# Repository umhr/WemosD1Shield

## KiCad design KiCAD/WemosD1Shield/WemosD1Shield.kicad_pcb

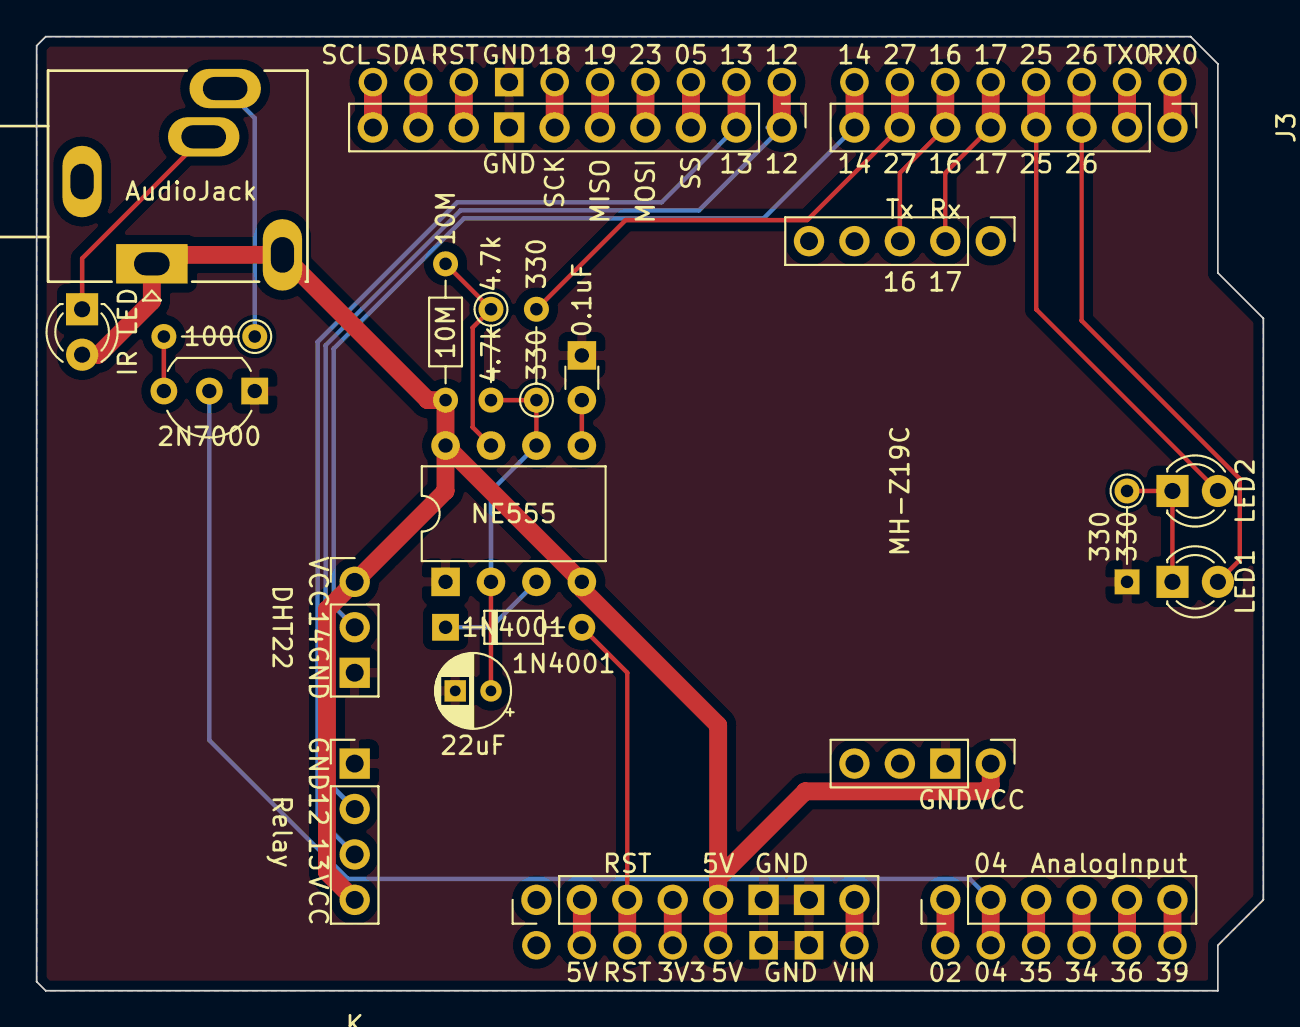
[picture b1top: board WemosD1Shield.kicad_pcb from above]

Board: 2 copper layers, 68.6 x 53.3 mm, 23 parts (1 on the bottom side), 37 nets.

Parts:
0.1uF: 0.1uF; C_Disc_D3.0mm_W1.6mm_P2.50mm
1N4001: 1N4001; D_DO-34_SOD68_P7.62mm_Horizontal
2N7000: Q_NPN_EBC; TO-92_Inline_Wide
04: Conn_01x06; PinHeader_1x06_P2.54mm_Vertical
4.7k: 4.7k; R_Axial_DIN0204_L3.6mm_D1.6mm_P5.08mm_Vertical
10M: 10M; R_Axial_DIN0204_L3.6mm_D1.6mm_P7.62mm_Horizontal
22uF: 22uF; CP_Radial_D4.0mm_P2.00mm
100: R; R_Axial_DIN0204_L3.6mm_D1.6mm_P5.08mm_Vertical
330, 330#2: 330; R_Axial_DIN0204_L3.6mm_D1.6mm_P5.08mm_Vertical
A1: Arduino_UNO_R3
AudioJack: AudioJack3_SwitchTR; Jack_3.5mm_Ledino_KB3SPRS_Horizontal
DHT22: DHT22; PinHeader_1x03_P2.54mm_Vertical
IR LED: LED; LED_D3.0mm_Clear
J3: Conn_01x08; PinHeader_1x08_P2.54mm_Vertical
J4: Conn_01x10; PinHeader_1x10_P2.54mm_Vertical
LED1, LED2: IR204A; LED_D3.0mm_IRBlack
NE555: NE555P; DIP-8_W7.62mm
RST: Conn_01x08; PinHeader_1x08_P2.54mm_Vertical
Relay: Relay; PinHeader_1x04_P2.54mm_Vertical
Rx: MH-Z19C; PinHeader_1x05_P2.54mm_Vertical
VCC: MH-Z19C; PinHeader_1x04_P2.54mm_Vertical

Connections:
GND: 0.1uF.2, 2N7000.1, 22uF.2, 330.2, A1.6, A1.7, A1.29, DHT22.3, J4.7, NE555.1, RST.6, RST.7, Relay.1, VCC.2
unnamed: A1.2, RST.2
unnamed: 1N4001.2, A1.3, RST.3
unnamed: A1.4, RST.4
unnamed: A1.8, RST.8
unnamed: 04.1, A1.9
unnamed: 2N7000.2, 04.2, A1.10
unnamed: 04.3, A1.11
unnamed: 04.4, A1.12
unnamed: 04.5, A1.13
unnamed: 04.6, A1.14
unnamed: A1.15, J3.1
unnamed: A1.16, J3.2
unnamed: A1.17, J3.3, LED1.2
unnamed: A1.18, J3.4, LED2.2
unnamed: A1.19, J3.5, Rx.2
unnamed: A1.20, J3.6, Rx.3
unnamed: 330#2.2, A1.21, J3.7
unnamed: A1.22, DHT22.2, J3.8
unnamed: A1.23, J4.1, Relay.2
unnamed: A1.24, J4.2, Relay.3
unnamed: A1.25, J4.3
unnamed: A1.26, J4.4
unnamed: A1.27, J4.5
unnamed: A1.28, J4.6
unnamed: A1.30, J4.8
unnamed: A1.31, J4.9
unnamed: A1.32, J4.10
unnamed: 4.7k.2, 22uF.1, 330#2.1, NE555.2, NE555.6
unnamed: 0.1uF.1, NE555.5
unnamed: 330.1, LED1.1, LED2.1
unnamed: 1N4001.1, NE555.3
unnamed: AudioJack.RN, IR LED.1
unnamed: 100.1, AudioJack.R
unnamed: 2N7000.3, 100.2
unnamed: 4.7k.1, 10M.2, NE555.7
VCC: 10M.1, A1.5, AudioJack.T, AudioJack.TN, DHT22.1, IR LED.2, NE555.4, NE555.8, RST.5, Relay.4, VCC.1

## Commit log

2022-07-09 ledによる接続表示
